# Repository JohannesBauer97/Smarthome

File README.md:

# Smarthome

Playing around with smarthome/internet of things technologies, concepts and hardware.

## Folder Structure
* Archiv
  * Old ESP8266 Sketches
* Hass.io
  * Homeassistant Project (deprecated)
* Selfmade
  * Current Smarthome System

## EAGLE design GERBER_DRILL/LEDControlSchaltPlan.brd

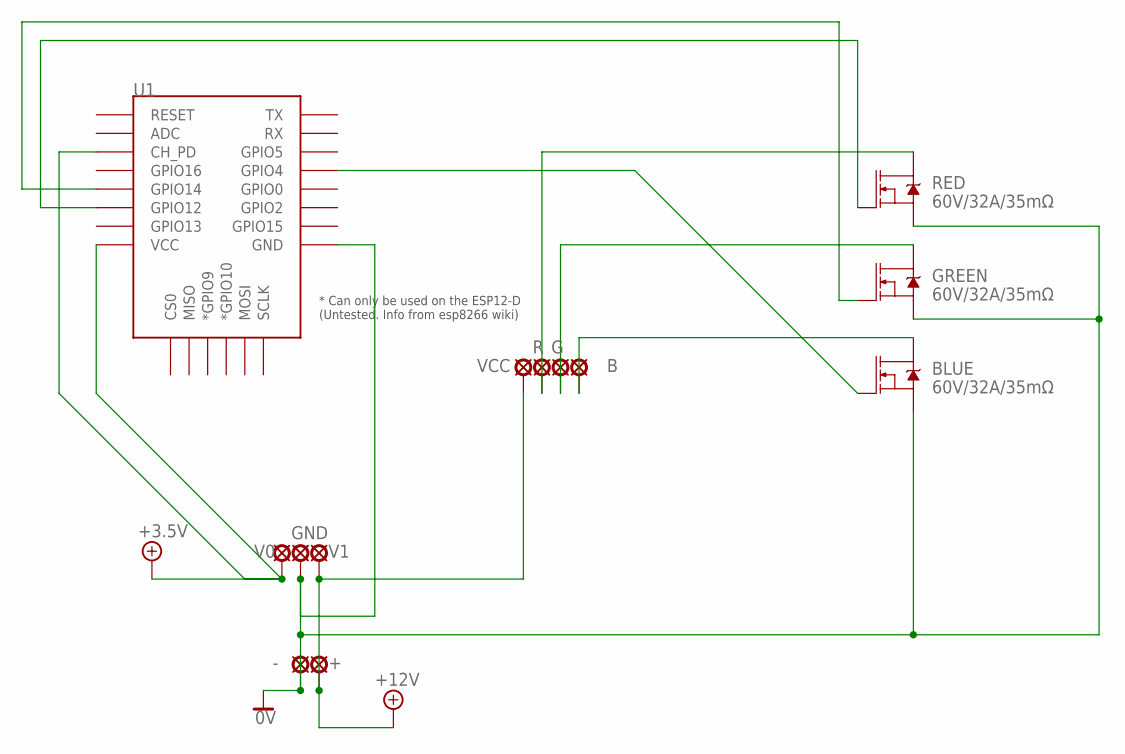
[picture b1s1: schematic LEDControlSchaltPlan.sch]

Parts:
+: LSP10
-: LSP10
B: LSP10
BLUE: 60V/32A/35mΩ; TO220V
G: LSP10
GND: LSP10
GREEN: 60V/32A/35mΩ; TO220V
R: LSP10
RED: 60V/32A/35mΩ; TO220V
U1: ESP12ESMD; ESP12E-SMD
V0, V1: LSP10
VCC: LSP10

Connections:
0V: -.MP, BLUE.3 (S), GND.MP, GREEN.3 (S), RED.3 (S), U1.GND
+5V: U1.CH_PD, U1.VCC, V0.MP
+12V: +.MP, V1.MP, VCC.MP
unnamed: RED.1 (G), U1.GPIO12
unnamed: GREEN.1 (G), U1.GPIO14
unnamed: BLUE.1 (G), U1.GPIO4
unnamed: R.MP, RED.2 (D)
unnamed: G.MP, GREEN.2 (D)
unnamed: B.MP, BLUE.2 (D)

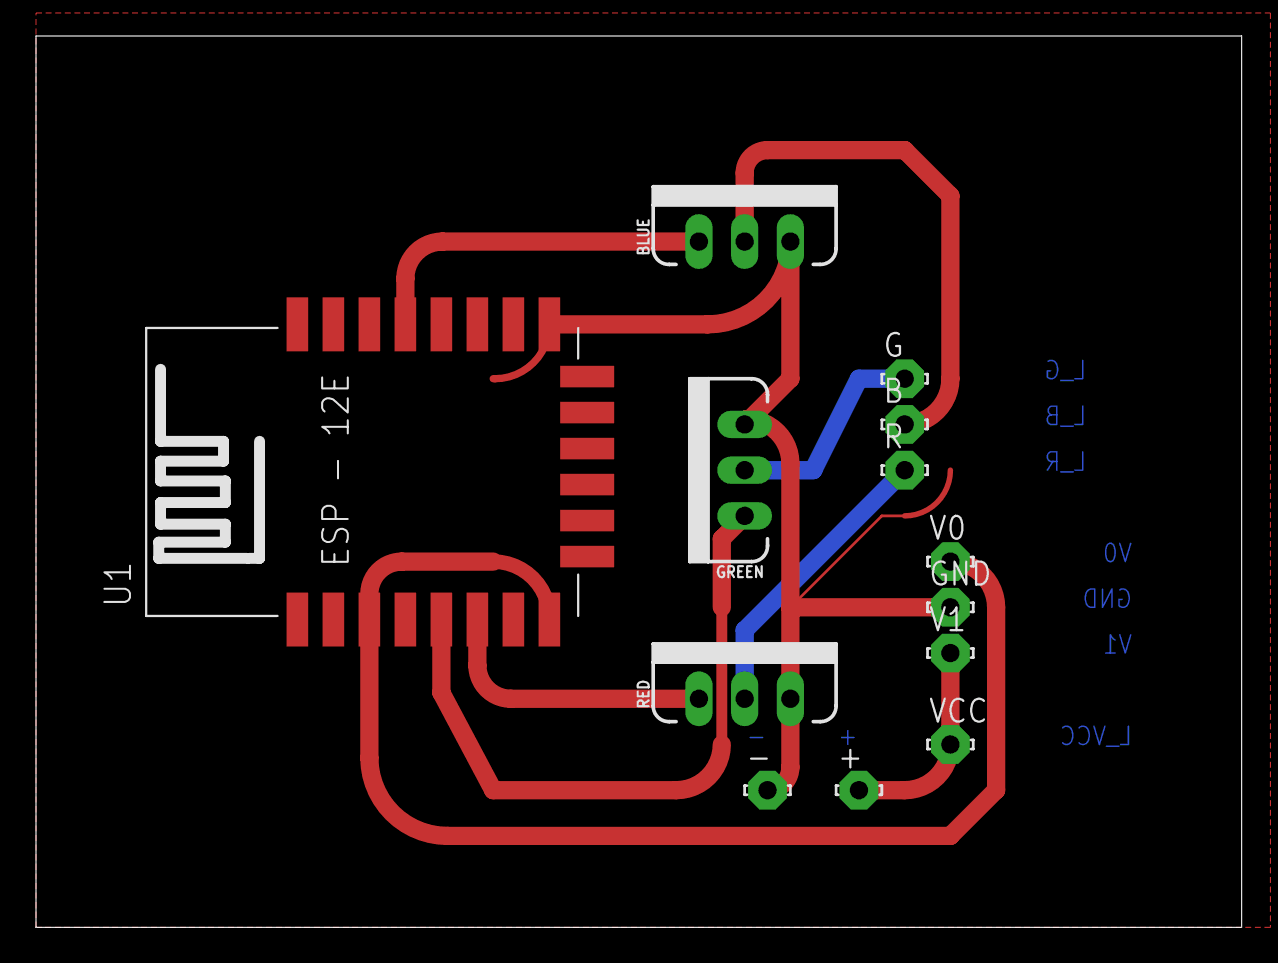
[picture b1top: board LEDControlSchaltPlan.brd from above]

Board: 2 copper layers, 67.0 x 49.5 mm, 13 parts (0 on the bottom side), 9 nets.

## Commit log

2017-11-03 init
2017-12-08 NodeServerV1, BasicWebClient
2017-12-08 For testing only: Mocked LED Client
2017-12-08 remove node_modules from _other/srv
2017-12-08 _other Folder structured
2017-12-08 Added Schaltplan
2017-12-10 AngularWebClient init
2017-12-13 Test Commit from Webstorm
2017-12-20 Navbar
2017-12-20 Navbar unversioned files
2018-01-17 LEDSketchV2
2018-01-28 WebClient added
2018-02-04 PCB Design
2018-08-12 Funktioniert
2018-08-12 Commit war falsch
2018-08-12 Adress Anpassungen
2018-08-12 Übergangsweise Path Route angepasst
2018-08-13 LEDSketch fixed burning led
2018-08-14 Reorder Folder
2018-08-14 Moved to subfolder
2018-08-18 Create LICENSE
2018-08-22 Init UIService, Added LEDService
2018-08-22 Added TCPServer
2018-09-28 Started using Hass.io
2018-09-28 Adding config files
2018-09-28 fixed update.sh
2018-09-29 Updated Configs
2018-09-29 Added lovelace ui
2018-09-29 Fixed Investments
2018-09-30 Added my tv led stripe
2018-09-30 Added tv led strip sketch
2018-10-03 Added Room & Bath Sensor
2018-10-07 Added Loft Sensor
2018-10-08 Added device to home card
2018-11-24 Added docker support
2019-01-27 Added Google Home
2020-05-07 Added new temp sketch and server
2020-05-07 Bump https-proxy-agent from 2.2.1 to 2.2.4 in /Archiv/WebClient
    Bumps [https-proxy-agent](https://github.com/TooTallNate/node-https-proxy-agent) from 2.2.1 to 2.2.4.
    - [Release notes](https://github.com/TooTallNate/node-https-proxy-agent/releases)
    - [Commits](https://github.com/TooTallNate/node-https-proxy-agent/compare/2.2.1...2.2.4)
2020-05-07 Bump mixin-deep from 1.3.1 to 1.3.2 in /Archiv/WebClient
    Bumps [mixin-deep](https://github.com/jonschlinkert/mixin-deep) from 1.3.1 to 1.3.2.
    - [Release notes](https://github.com/jonschlinkert/mixin-deep/releases)
    - [Commits](https://github.com/jonschlinkert/mixin-deep/compare/1.3.1...1.3.2)
2020-05-07 Bump acorn from 5.7.1 to 5.7.4 in /Archiv/WebClient
    Bumps [acorn](https://github.com/acornjs/acorn) from 5.7.1 to 5.7.4.
    - [Release notes](https://github.com/acornjs/acorn/releases)
    - [Commits](https://github.com/acornjs/acorn/compare/5.7.1...5.7.4)
2020-05-07 Bump handlebars from 4.0.11 to 4.7.6 in /Archiv/WebClient
    Bumps [handlebars](https://github.com/wycats/handlebars.js) from 4.0.11 to 4.7.6.
    - [Release notes](https://github.com/wycats/handlebars.js/releases)
    - [Changelog](https://github.com/handlebars-lang/handlebars.js/blob/master/release-notes.md)
    - [Commits](https://github.com/wycats/handlebars.js/compare/v4.0.11...v4.7.6)
2020-05-08 restructure
2020-05-08 did some more stuff on server
2020-05-09 updated autodiscover
2020-05-09 Added swagger
2020-05-09 broker and client
2020-05-17 added gitignore
2020-05-17 removed useless tracked files
2020-05-26 idk anymore
2020-05-26 removed some logging
2020-05-26 added sqlite database
2020-05-26 added ReSubscribe
2020-05-27 removed db tracking
2020-05-27 added null checks
2020-05-27 sketch updates
2020-05-27 removed discovered from db
2020-05-27 added webui + logging
2020-05-27 reformat favicon
2020-05-27 favicon
2020-05-27 webui
2020-05-28 angular hosting + dockerfile
2020-05-28 updated docker stuff
2020-05-28 using datafolder for persistent files
2020-05-28 Updated dockerfiles
2020-05-28 Added renaming feature
2020-06-06 Bump websocket-extensions from 0.1.3 to 0.1.4 in /Archiv/WebClient
    Bumps [websocket-extensions](https://github.com/faye/websocket-extensions-node) from 0.1.3 to 0.1.4.
    - [Release notes](https://github.com/faye/websocket-extensions-node/releases)
    - [Changelog](https://github.com/faye/websocket-extensions-node/blob/master/CHANGELOG.md)
    - [Commits](https://github.com/faye/websocket-extensions-node/compare/0.1.3...0.1.4)
2020-06-08 Bump websocket-extensions in /Selfmade/SmartServer/webui
    Bumps [websocket-extensions](https://github.com/faye/websocket-extensions-node) from 0.1.3 to 0.1.4.
    - [Release notes](https://github.com/faye/websocket-extensions-node/releases)
    - [Changelog](https://github.com/faye/websocket-extensions-node/blob/master/CHANGELOG.md)
    - [Commits](https://github.com/faye/websocket-extensions-node/compare/0.1.3...0.1.4)
2020-07-08 Bump npm-registry-fetch in /Selfmade/SmartServer/webui
    Bumps [npm-registry-fetch](https://github.com/npm/registry-fetch) from 4.0.4 to 4.0.5.
    - [Release notes](https://github.com/npm/registry-fetch/releases)
    - [Changelog](https://github.com/npm/npm-registry-fetch/blob/latest/CHANGELOG.md)
    - [Commits](https://github.com/npm/registry-fetch/commits)
2020-07-20 Bump lodash from 4.17.15 to 4.17.19 in /Selfmade/SmartServer/webui
    Bumps [lodash](https://github.com/lodash/lodash) from 4.17.15 to 4.17.19.
    - [Release notes](https://github.com/lodash/lodash/releases)
    - [Commits](https://github.com/lodash/lodash/compare/4.17.15...4.17.19)
2020-07-30 Bump elliptic from 6.4.0 to 6.5.3 in /Archiv/WebClient
    Bumps [elliptic](https://github.com/indutny/elliptic) from 6.4.0 to 6.5.3.
    - [Release notes](https://github.com/indutny/elliptic/releases)
    - [Commits](https://github.com/indutny/elliptic/compare/v6.4.0...v6.5.3)
2020-08-02 Bump elliptic from 6.5.2 to 6.5.3 in /Selfmade/SmartServer/webui
    Bumps [elliptic](https://github.com/indutny/elliptic) from 6.5.2 to 6.5.3.
    - [Release notes](https://github.com/indutny/elliptic/releases)
    - [Commits](https://github.com/indutny/elliptic/compare/v6.5.2...v6.5.3)
2020-09-04 Bump node-sass from 4.9.2 to 4.14.1 in /Archiv/WebClient
    Bumps [node-sass](https://github.com/sass/node-sass) from 4.9.2 to 4.14.1.
    - [Release notes](https://github.com/sass/node-sass/releases)
    - [Changelog](https://github.com/sass/node-sass/blob/master/CHANGELOG.md)
    - [Commits](https://github.com/sass/node-sass/compare/v4.9.2...v4.14.1)
2020-09-04 Bump lodash.mergewith from 4.6.1 to 4.6.2 in /Archiv/WebClient
    Bumps [lodash.mergewith](https://github.com/lodash/lodash) from 4.6.1 to 4.6.2.
    - [Release notes](https://github.com/lodash/lodash/releases)
    - [Commits](https://github.com/lodash/lodash/commits)
2020-09-05 Bump tree-kill from 1.2.0 to 1.2.2 in /Archiv/WebClient
    Bumps [tree-kill](https://github.com/pkrumins/node-tree-kill) from 1.2.0 to 1.2.2.
    - [Release notes](https://github.com/pkrumins/node-tree-kill/releases)
    - [Commits](https://github.com/pkrumins/node-tree-kill/compare/v1.2.0...v1.2.2)
2020-09-06 Bump http-proxy from 1.17.0 to 1.18.1 in /Archiv/WebClient
    Bumps [http-proxy](https://github.com/http-party/node-http-proxy) from 1.17.0 to 1.18.1.
    - [Release notes](https://github.com/http-party/node-http-proxy/releases)
    - [Changelog](https://github.com/http-party/node-http-proxy/blob/master/CHANGELOG.md)
    - [Commits](https://github.com/http-party/node-http-proxy/compare/1.17.0...1.18.1)
2020-10-19 Bump webpack-subresource-integrity in /Archiv/WebClient
    Bumps [webpack-subresource-integrity](https://github.com/waysact/webpack-subresource-integrity) from 1.1.0-rc.4 to 1.5.1.
    - [Release notes](https://github.com/waysact/webpack-subresource-integrity/releases)
    - [Changelog](https://github.com/waysact/webpack-subresource-integrity/blob/master/CHANGELOG.md)
    - [Commits](https://github.com/waysact/webpack-subresource-integrity/compare/v1.1.0-rc.4...v1.5.1)

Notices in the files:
parts and their libraries:
SparkFun-DiscreteSemi: Licensing: Creative Commons ShareAlike 4.0 International - https://creativecommons.org/licenses/by-sa/4.0
